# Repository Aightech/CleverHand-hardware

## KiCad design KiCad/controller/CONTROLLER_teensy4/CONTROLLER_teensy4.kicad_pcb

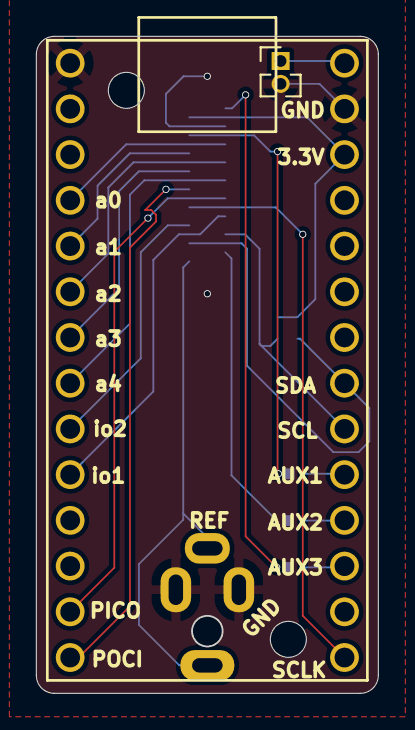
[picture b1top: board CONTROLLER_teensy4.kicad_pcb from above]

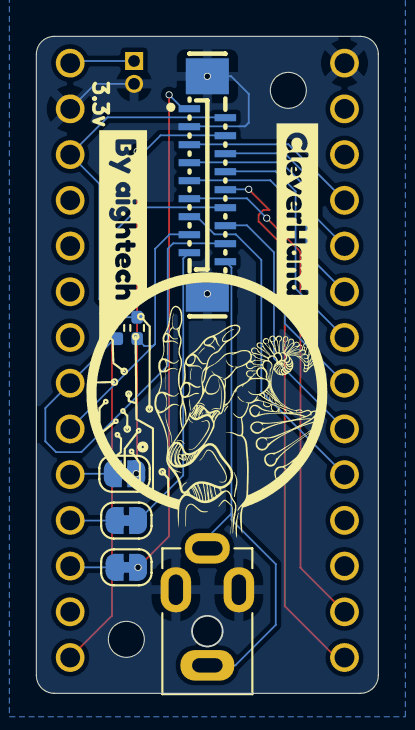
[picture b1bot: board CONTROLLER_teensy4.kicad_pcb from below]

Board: 4 copper layers, 19.0 x 36.5 mm, 11 parts (9 on the bottom side), 22 nets.

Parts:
FPC1: FPC-05F-18PH20; FPC-SMD_18P-P0.50_X05C2018TZ
J2: Conn_01x02_Pin; PinHeader_1x02_P1.27mm_Vertical
J5: jack2.5_PJ-210B; Jack_Socket_PJ-210B
JP1, JP2, JP3: SolderJumper_2_Bridged; SolderJumper-2_P1.3mm_Bridged_RoundedPad1.0x1.5mm
R1, R2: 2k; R_0402_1005Metric_Pad0.72x0.64mm_HandSolder
U1: Teensy4.0; Teensy40_simple
kibuzzard-6611AB09: G***; kibuzzard-6611AB09
kibuzzard-6611ABB8: G***; kibuzzard-6611ABB8

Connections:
+3.3V: FPC1.2, R1.1, R2.1, U1.31 (3V3)
/AUX1: FPC1.1, JP1.1 (A)
/AUX2: FPC1.17, JP2.1 (A)
/AUX3: FPC1.4, JP3.1 (A)
/I2C_SDA: FPC1.15, R2.2, U1.25 (18_A4_SDA0)
/IO1_out: FPC1.13, U1.10 (8_TX2_IN1)
/IO2: FPC1.14, U1.9 (7_RX2_OUT1A)
/PICO: FPC1.11, U1.13 (11_MOSI_CTX1)
/POCI: FPC1.10, U1.14 (12_MISO_MQSL)
/SCLK: FPC1.12, U1.20 (13_SCK_CRX1_LED)
/addr_bus_0: FPC1.5, U1.4 (2_OUT2)
/addr_bus_1: FPC1.6, U1.5 (3_LRCLK2)
/addr_bus_2: FPC1.7, U1.6 (4_BCLK2)
/addr_bus_3: FPC1.8, U1.7 (5_IN2)
/addr_bus_4: FPC1.9, U1.8 (6_OUT1D)
/extRef: FPC1.18, J5.2 (R), J5.6 (S)
/i2C_SCL: FPC1.16, R1.2, U1.26 (19_A5_SCL0)
GND: FPC1.3, FPC1.19, FPC1.20, J2.2, J5.1 (T), J5.3 (T), U1.1 (GND), U1.32 (GND)
unnamed: JP1.2 (B), U1.22 (15_A1_RX3_SPDIF_IN)
unnamed: JP2.2 (B), U1.23 (16_A2_RX4_SCL1)
unnamed: JP3.2 (B), U1.24 (17_A3_TX4_SDA1)
VSYS: J2.1, U1.33 (VIN)

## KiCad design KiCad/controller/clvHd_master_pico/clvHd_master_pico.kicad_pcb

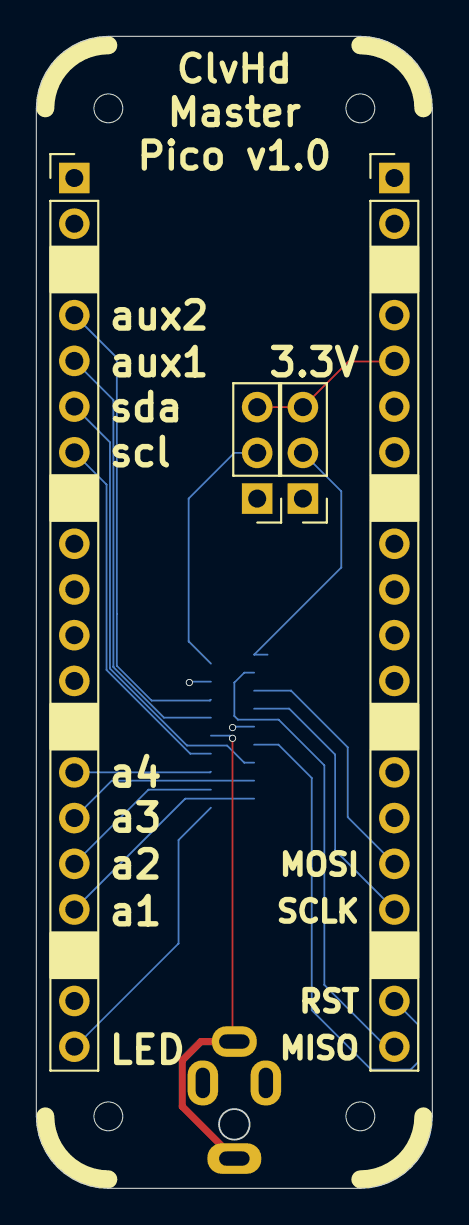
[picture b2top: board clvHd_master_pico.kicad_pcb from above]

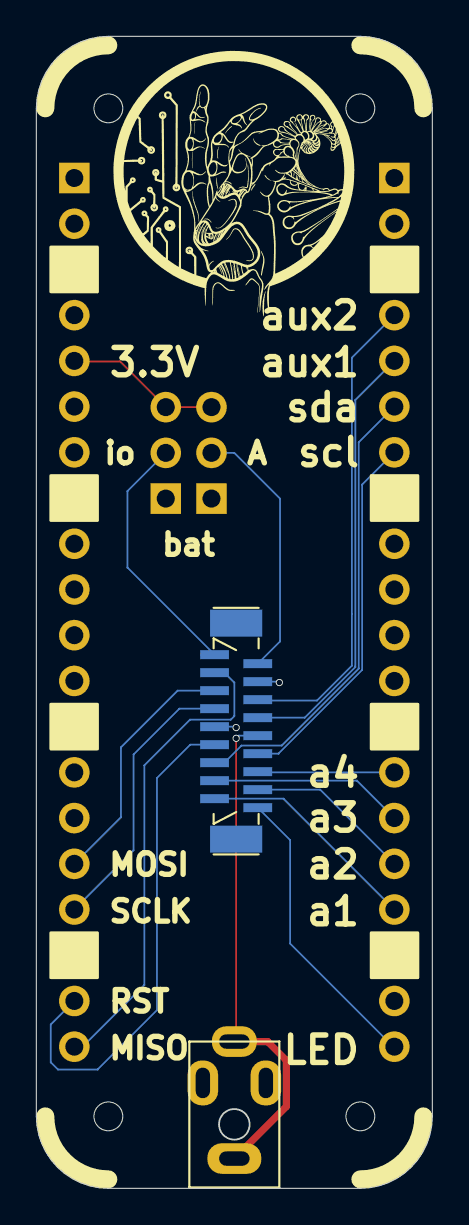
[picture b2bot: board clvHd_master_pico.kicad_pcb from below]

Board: 4 copper layers, 22.0 x 64.0 mm, 6 parts (2 on the bottom side), 18 nets.

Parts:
J1: XF2J-1824-12A
J3: jack2.5_PJ-210B; Jack_Socket_PJ-210B
J4, J5: Conn_01x20_Male; PinHeader_1x20_P2.54mm_Vertical
J6, J7: Conn_01x03_Male; PinHeader_1x03_P2.54mm_Vertical

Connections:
3V3_PICO: J5.5, J6.3, J7.3
+3.3V: J1.1, J7.2
+5VA: J1.2, J6.2
ADD_OUT1: J1.17, J4.17
ADD_OUT2: J1.16, J4.16
ADD_OUT3: J1.15, J4.15
ADD_OUT4: J1.14, J4.14
AUX1: J1.8, J4.5
AUX2: J1.6, J4.4
GND: J1.4, J1.9, J3.1 (T), J3.3 (T), J4.3, J4.8, J4.13, J4.18, J5.3, J5.8, J5.13, J5.18
I2C_SCL: J1.12, J4.7
I2C_SDA: J1.13, J4.6
IN_ref: J1.10, J3.2 (R), J3.6 (S)
LED_OUT: J1.18, J4.20
MISO_DOUT: J1.3, J5.20
MOSI_DIN: J1.5, J5.16
RESETB: J1.11, J5.19
SCLK: J1.7, J5.17

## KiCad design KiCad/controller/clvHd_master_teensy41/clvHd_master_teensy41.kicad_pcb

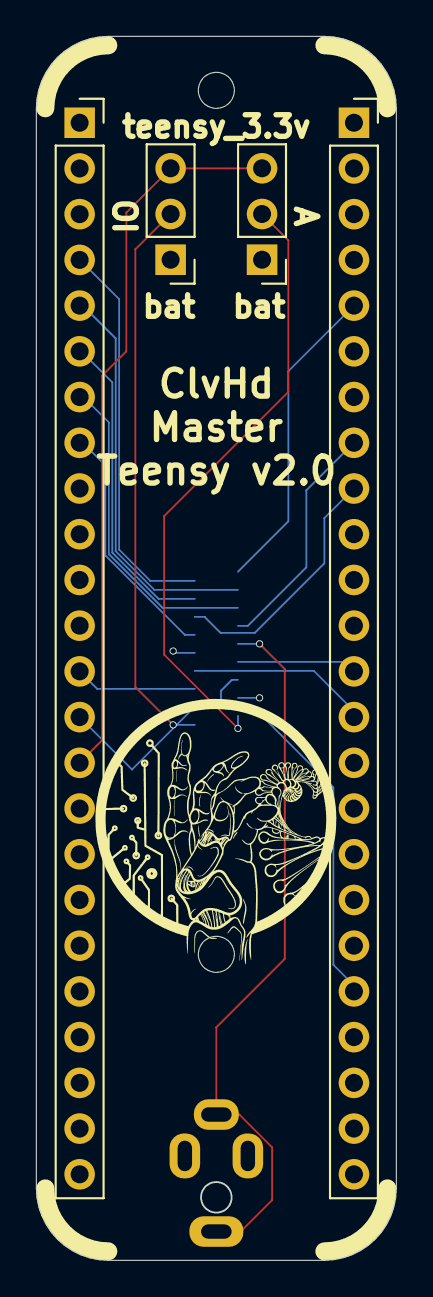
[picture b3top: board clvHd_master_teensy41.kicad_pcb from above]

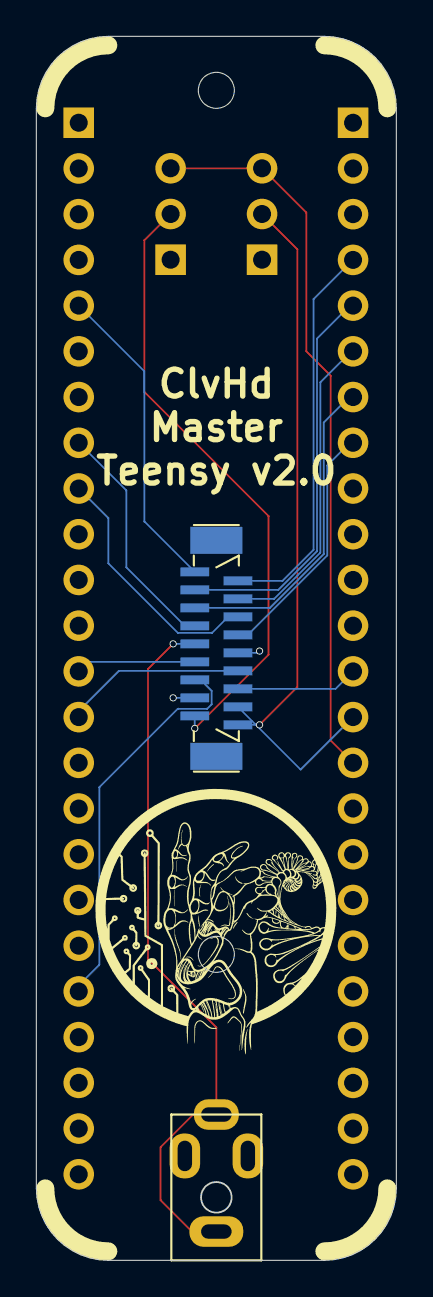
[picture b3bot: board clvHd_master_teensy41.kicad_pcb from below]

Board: 4 copper layers, 20.0 x 68.0 mm, 6 parts (2 on the bottom side), 18 nets.

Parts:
J1: XF2J-1824-12A
J2, J6: Conn_01x03_Male; PinHeader_1x03_P2.54mm_Vertical
J3: teensy_right; PinSocket_1x24_P2.54mm_Vertical
J4: teensy_left; PinSocket_1x24_P2.54mm_Vertical
J5: jack2.5_PJ-210B; Jack_Socket_PJ-210B

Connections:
3V3_TEENSY: J2.3, J4.15, J6.3
+3.3V: J1.1, J6.2
+5VA: J1.2, J2.2
ADD_OUT1: J1.17, J4.4
ADD_OUT2: J1.16, J4.5
ADD_OUT3: J1.15, J4.6
ADD_OUT4: J1.14, J4.7
AUX1: J1.8, J3.13
AUX2: J1.6, J3.20
GND: J1.4, J1.9, J3.2, J3.15, J4.1, J5.1 (T), J5.3 (T)
I2C_SCL: J1.12, J3.8
I2C_SDA: J1.13, J3.9
IN_ref: J1.10, J5.2 (R), J5.6 (S)
LED_OUT: J1.18, J3.5
MISO_DOUT: J1.3, J4.14
MOSI_DIN: J1.5, J4.13
RESETB: J1.11, J4.8
SCLK: J1.7, J3.14

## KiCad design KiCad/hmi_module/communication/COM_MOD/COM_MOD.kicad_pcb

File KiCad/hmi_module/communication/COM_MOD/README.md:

# Communication Module
This module is responsible for handling the communication between the different modules of the controller node.

The communication bus is composed of :
- Power supply (3.3V) and ground
- SPI bus (POCI, PICO, SCK)
- I2C bus (SDA, SCL)
- Address bus (A0, A1, A2, A3, A4)
- External reference voltage (AREF)

When the module is connected to the bus, it is assigned an address by the controller node. This address is used to identify the module on the bus.
The communication module will activate the chip select line of the associated sensor module when the address bus matches its address.
Additionally, each module has a unique identifier that is used to identify the module on the I2C bus.

## Electrical Schematic

## PCB Layout

## 3D Model

```stl
// COM_MOD_pcb.stl

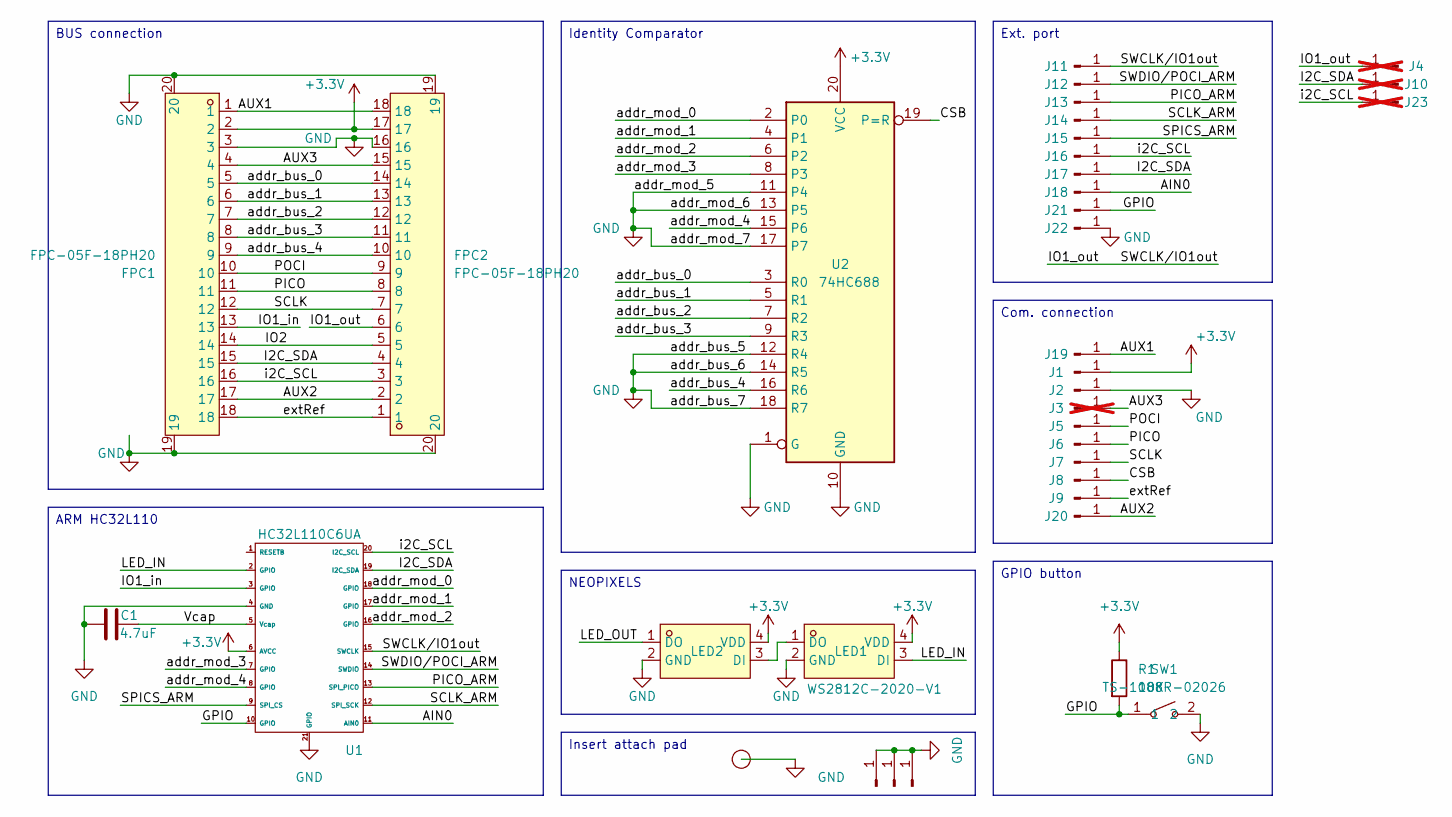
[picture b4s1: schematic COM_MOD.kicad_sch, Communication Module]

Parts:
C1: 4.7uF; C_0402_1005Metric; LCSC C23733
FPC1, FPC2: FPC-05F-18PH20; FPC-SMD_18P-P0.50_FPC-05F-18PH20; LCSC Part C2856802
I1: smd_insert; insert_1.2mm
J1, J2, J5, J6, J7, J8, J9, J11, J12, J13, J14, J15, J16, J17, J18, J19, J20, J21, J22: Conn_01x01_Pin; PinHeader_1x01_P1.27mm_Vertical
J3, J4, J10, J23: Conn_01x01_Pin; PinHeader_1x01_P1.27mm_Vertical; not fitted
J24, J25, J26: Conn_01x01_Pin; PinSocket_1x01_P2.54mm_Vertical
LED1: WS2812C-2020-V1; LED-SMD_4P-L2.0-W2.0-TL_WS2812B-2020; LCSC Part C2976072
LED2: WS2812C; LED-SMD_4P-L2.0-W2.0-TL_WS2812B-2020; LCSC Part C2976072
R1: 10K; R_0402_1005Metric; LCSC C25744
SW1: TS-1088R-02026; SW-SMD_L3.9-W3.0-P4.45; LCSC Part C455280
U1: HC32L110C6UA; QFN-20-1EP_3x3mm_P0.4mm_EP1.4x1.4mm; LCSC C493490
U2: 74HC688; TSSOP-20_W4.4mm; LCSC C132045

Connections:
+3.3V: FPC1.2, FPC2.17, J1.1, LED1.4 (VDD), LED2.4 (VDD), R1.1, U1.6 (AVCC), U2.20 (VCC)
/AIN0: J18.1, U1.11 (AIN0)
/AUX1: FPC1.1, FPC2.18, J19.1
/AUX2: FPC1.17, FPC2.2, J20.1
/AUX3: FPC1.4, FPC2.15, J3.1
/CSB: J8.1, U2.19 (P=R)
/GPIO: J21.1, R1.2, SW1.1, U1.10 (GPIO)
/I2C_SDA: FPC1.15, FPC2.4, J10.1, J17.1, U1.19 (I2C_SDA)
/IO1_in: FPC1.13, U1.3 (GPIO)
/IO1_out: FPC2.6, J4.1, J11.1, U1.15 (SWCLK)
/IO2: FPC1.14, FPC2.5
/LED_IN: LED1.3 (DI), U1.2 (GPIO)
/LED_OUT: LED2.1 (DO)
/PICO: FPC1.11, FPC2.8, J6.1
/PICO_ARM: J13.1, U1.13 (SPI_PICO)
/POCI: FPC1.10, FPC2.9, J5.1
/SCLK: FPC1.12, FPC2.7, J7.1
/SCLK_ARM: J14.1, U1.12 (SPI_SCK)
/SPICS_ARM: J15.1, U1.9 (SPI_CS)
/SWDIO/POCI_ARM: J12.1, U1.14 (SWDIO)
/Vcap: C1.2, U1.5 (Vcap)
/addr_bus_0: FPC1.5, FPC2.14, U2.3 (R0)
/addr_bus_1: FPC1.6, FPC2.13, U2.5 (R1)
/addr_bus_2: FPC1.7, FPC2.12, U2.7 (R2)
/addr_bus_3: FPC1.8, FPC2.11, U2.9 (R3)
/addr_bus_4: FPC1.9, FPC2.10, U2.16 (R6)
/addr_mod_0: U1.18 (GPIO), U2.2 (P0)
/addr_mod_1: U1.17 (GPIO), U2.4 (P1)
/addr_mod_2: U1.16 (GPIO), U2.6 (P2)
/addr_mod_3: U1.7 (GPIO), U2.8 (P3)
/addr_mod_4: U1.8 (GPIO), U2.15 (P6)
/extRef: FPC1.18, FPC2.1, J9.1
/i2C_SCL: FPC1.16, FPC2.3, J16.1, J23.1, U1.20 (I2C_SCL)
GND: C1.1, FPC1.3, FPC1.19, FPC1.20, FPC2.16, FPC2.19, FPC2.20, I1.1 (conn), J2.1, J22.1, J24.1, J25.1, J26.1, LED1.2 (GND), LED2.2 (GND), SW1.2, U1.4 (GND), U1.21 (GPIO), U2.1 (G), U2.10 (GND), U2.11 (P4), U2.12 (R4), U2.13 (P5), U2.14 (R5), U2.17 (P7), U2.18 (R7)
unnamed: LED1.1 (DO), LED2.3 (DI)

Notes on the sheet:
ARM HC32L110
Insert attach pad
NEOPIXELS
Identity Comparator
Com. connection
GPIO button
BUS connection
Ext. port

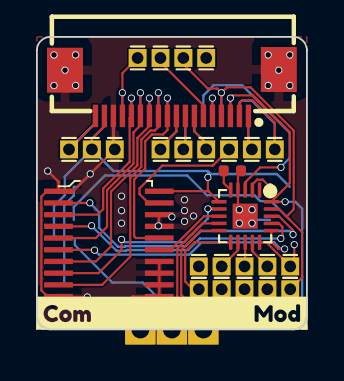
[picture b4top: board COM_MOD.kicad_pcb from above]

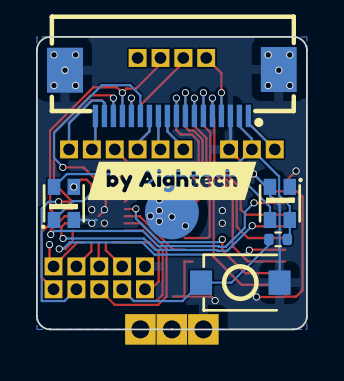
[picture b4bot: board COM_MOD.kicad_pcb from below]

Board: 4 copper layers, 15.0 x 16.3 mm, 38 parts (7 on the bottom side), 34 nets.

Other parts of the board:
kibuzzard-658C3FF8: G***; kibuzzard-658C3FF8
kibuzzard-658C2757: G***; kibuzzard-658C2757

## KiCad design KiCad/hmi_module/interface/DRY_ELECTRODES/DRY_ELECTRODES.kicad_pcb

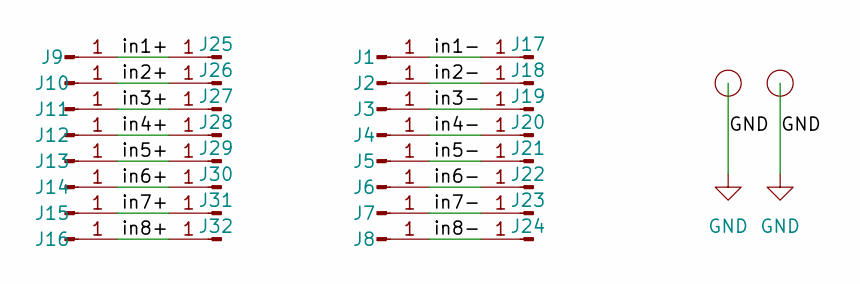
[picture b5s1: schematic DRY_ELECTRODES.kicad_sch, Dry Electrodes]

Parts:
I3, I4: smd_insert; insert_1.2mm
J1, J2, J3, J4, J5, J6, J7, J8, J9, J10, J11, J12, J13, J14, J15, J16: Conn_01x01_Pin; SolderWirePad_1x01_SMD_1x2mm
J17, J18, J19, J20, J21, J22, J23, J24, J25, J26, J27, J28, J29, J30, J31, J32: Conn_01x01_Pin; Pin_D1.2mm_pogo

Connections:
/in1+: J9.1, J25.1
/in1-: J1.1, J17.1
/in2+: J10.1, J26.1
/in2-: J2.1, J18.1
/in3+: J11.1, J27.1
/in3-: J3.1, J19.1
/in4+: J12.1, J28.1
/in4-: J4.1, J20.1
/in5+: J13.1, J29.1
/in5-: J5.1, J21.1
/in6+: J14.1, J30.1
/in6-: J6.1, J22.1
/in7+: J15.1, J31.1
/in7-: J7.1, J23.1
/in8+: J16.1, J32.1
/in8-: J8.1, J24.1
GND: I3.1 (conn), I4.1 (conn)

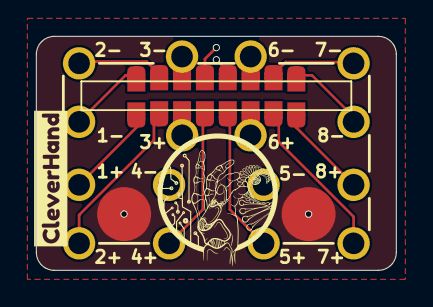
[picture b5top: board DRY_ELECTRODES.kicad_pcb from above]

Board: 4 copper layers, 20.0 x 13.0 mm, 35 parts (0 on the bottom side), 17 nets.

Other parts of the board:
kibuzzard-660706DE: G***; kibuzzard-660706DE

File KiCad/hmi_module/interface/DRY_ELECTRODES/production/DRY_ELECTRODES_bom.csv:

"Reference","Value","Footprint","DNP","LCSC"
"I3","smd_insert","00_custom-footprints:insert_1.2mm","",""
"I4","smd_insert","00_custom-footprints:insert_1.2mm","",""
"J1","Conn_01x01_Pin","00_custom-footprints:SolderWirePad_1x01_SMD_1x2mm","",""
"J2","Conn_01x01_Pin","00_custom-footprints:SolderWirePad_1x01_SMD_1x2mm","",""
"J3","Conn_01x01_Pin","00_custom-footprints:SolderWirePad_1x01_SMD_1x2mm","",""
"J4","Conn_01x01_Pin","00_custom-footprints:SolderWirePad_1x01_SMD_1x2mm","",""
"J5","Conn_01x01_Pin","00_custom-footprints:SolderWirePad_1x01_SMD_1x2mm","",""
"J6","Conn_01x01_Pin","00_custom-footprints:SolderWirePad_1x01_SMD_1x2mm","",""
"J7","Conn_01x01_Pin","00_custom-footprints:SolderWirePad_1x01_SMD_1x2mm","",""
"J8","Conn_01x01_Pin","00_custom-footprints:SolderWirePad_1x01_SMD_1x2mm","",""
"J9","Conn_01x01_Pin","00_custom-footprints:SolderWirePad_1x01_SMD_1x2mm","",""
"J10","Conn_01x01_Pin","00_custom-footprints:SolderWirePad_1x01_SMD_1x2mm","",""
"J11","Conn_01x01_Pin","00_custom-footprints:SolderWirePad_1x01_SMD_1x2mm","",""
"J12","Conn_01x01_Pin","00_custom-footprints:SolderWirePad_1x01_SMD_1x2mm","",""
"J13","Conn_01x01_Pin","00_custom-footprints:SolderWirePad_1x01_SMD_1x2mm","",""
"J14","Conn_01x01_Pin","00_custom-footprints:SolderWirePad_1x01_SMD_1x2mm","",""
"J15","Conn_01x01_Pin","00_custom-footprints:SolderWirePad_1x01_SMD_1x2mm","",""
"J16","Conn_01x01_Pin","00_custom-footprints:SolderWirePad_1x01_SMD_1x2mm","",""
"J17","Conn_01x01_Pin","00_custom-footprints:Pin_D1.2mm_pogo","",""
"J18","Conn_01x01_Pin","00_custom-footprints:Pin_D1.2mm_pogo","",""
"J19","Conn_01x01_Pin","00_custom-footprints:Pin_D1.2mm_pogo","",""
"J20","Conn_01x01_Pin","00_custom-footprints:Pin_D1.2mm_pogo","",""
"J21","Conn_01x01_Pin","00_custom-footprints:Pin_D1.2mm_pogo","",""
"J22","Conn_01x01_Pin","00_custom-footprints:Pin_D1.2mm_pogo","",""
"J23","Conn_01x01_Pin","00_custom-footprints:Pin_D1.2mm_pogo","",""
"J24","Conn_01x01_Pin","00_custom-footprints:Pin_D1.2mm_pogo","",""
"J25","Conn_01x01_Pin","00_custom-footprints:Pin_D1.2mm_pogo","",""
"J26","Conn_01x01_Pin","00_custom-footprints:Pin_D1.2mm_pogo","",""
"J27","Conn_01x01_Pin","00_custom-footprints:Pin_D1.2mm_pogo","",""
"J28","Conn_01x01_Pin","00_custom-footprints:Pin_D1.2mm_pogo","",""
"J29","Conn_01x01_Pin","00_custom-footprints:Pin_D1.2mm_pogo","",""
"J30","Conn_01x01_Pin","00_custom-footprints:Pin_D1.2mm_pogo","",""
"J31","Conn_01x01_Pin","00_custom-footprints:Pin_D1.2mm_pogo","",""
"J32","Conn_01x01_Pin","00_custom-footprints:Pin_D1.2mm_pogo","",""

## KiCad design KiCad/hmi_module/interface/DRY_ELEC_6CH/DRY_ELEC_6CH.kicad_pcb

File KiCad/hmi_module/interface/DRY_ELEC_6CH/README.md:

# Dry Electrodes Module
This module is responsible for interfacing the sensors/actuators inputs/outputs with the user skin or with other modules.

## Electrical Schematic

## PCB Layout

## 3D Model

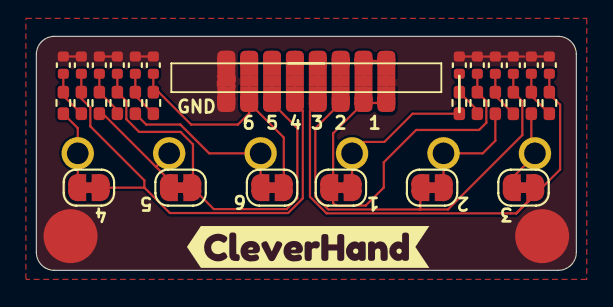
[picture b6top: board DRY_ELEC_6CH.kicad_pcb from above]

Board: 4 copper layers, 30.0 x 13.0 mm, 55 parts (0 on the bottom side), 19 nets.

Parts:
C1, C2, C3, C4, C5, C6, C7, C8, C9, C10, C11, C12: C; C_0402_1005Metric
I3, I4: smd_insert; insert_1.2mm
J1, J2, J3, J4, J5, J6, J7, J8, J9, J10, J11, J12, J13, J14, J15, J16: Conn_01x01_Pin; SolderWirePad_1x01_SMD_1x2mm
J17, J18, J19, J20, J21, J22: Conn_01x01_Pin; Pin_D1.2mm_pogo
JP1, JP2, JP3, JP4, JP5, JP6: SolderJumper_2_Bridged; SolderJumper-2_P1.3mm_Bridged_RoundedPad1.0x1.5mm
R1, R2, R3, R4, R5, R6, R7, R8, R9, R10, R11, R12: R; R_0402_1005Metric_Pad0.72x0.64mm_HandSolder
kibuzzard-66BA2E59: G***; kibuzzard-66BA2E59

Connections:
/IN1: C2.1, J7.1, J8.1, J15.1, J16.1, JP1.2 (B), R2.2
/IN2: C4.1, J6.1, J14.1, JP2.2 (B), R4.2
/IN3: C6.1, J5.1, J13.1, JP3.2 (B), R6.2
/IN4: C8.1, J4.1, J12.1, JP4.2 (B), R8.2
/IN5: C10.1, J3.1, J11.1, JP5.2 (B), R10.2
/IN6: C12.1, J2.1, J10.1, JP6.2 (B), R12.2
/filtering_1/ELECTRODE: J17.1, JP1.1 (A), R1.1
/filtering_2/ELECTRODE: J18.1, JP2.1 (A), R3.1
/filtering_3/ELECTRODE: J19.1, JP3.1 (A), R5.1
/filtering_4/ELECTRODE: J20.1, JP4.1 (A), R7.1
/filtering_5/ELECTRODE: J21.1, JP5.1 (A), R9.1
/filtering_6/ELECTRODE: J22.1, JP6.1 (A), R11.1
GND: C1.2, C2.2, C3.2, C4.2, C5.2, C6.2, C7.2, C8.2, C9.2, C10.2, C11.2, C12.2, I3.1 (conn), I4.1 (conn), J1.1, J9.1
unnamed: C1.1, R1.2, R2.1
unnamed: C3.1, R3.2, R4.1
unnamed: C5.1, R5.2, R6.1
unnamed: C7.1, R7.2, R8.1
unnamed: C9.1, R9.2, R10.1
unnamed: C11.1, R11.2, R12.1

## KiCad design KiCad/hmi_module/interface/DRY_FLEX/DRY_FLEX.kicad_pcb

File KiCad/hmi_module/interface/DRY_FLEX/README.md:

# Communication Module
This module extends the electrodes module. It a flexible PCB that connects the electrodes module and offers a flexible interface to the user.

## Electrical Schematic

## PCB Layout

## 3D Model

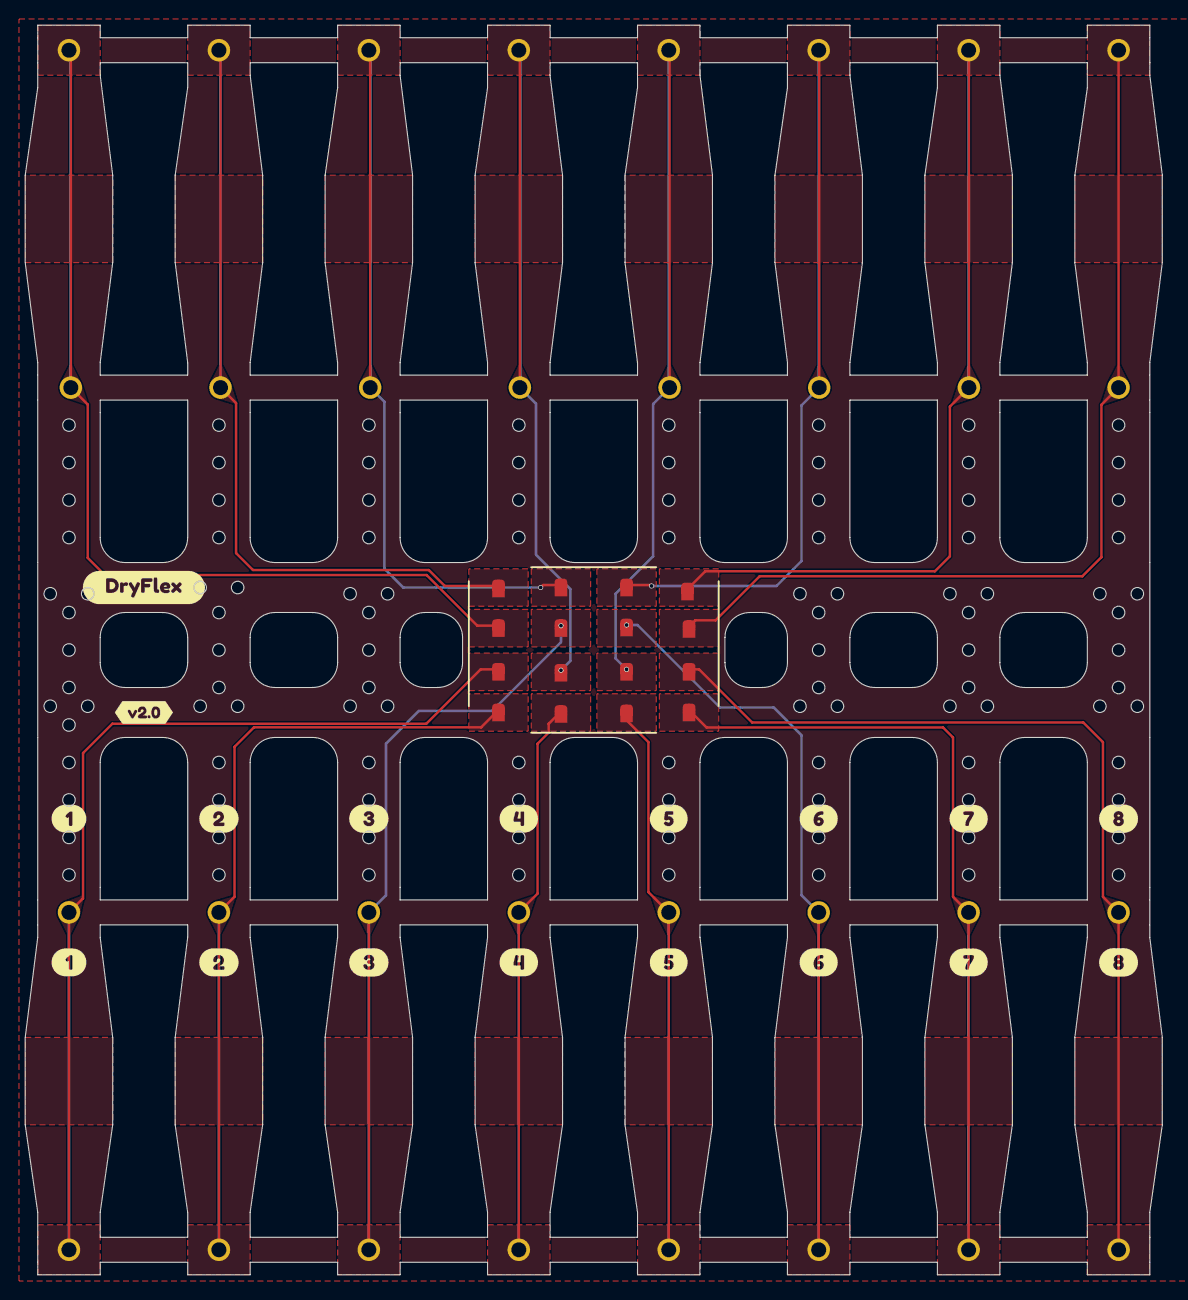
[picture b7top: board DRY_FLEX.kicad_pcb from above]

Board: 2 copper layers, 91.0 x 100.0 mm, 67 parts (1 on the bottom side), 16 nets.

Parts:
J1, J2, J3, J4, J5, J6, J7, J8, J9, J10, J11, J12, J13, J14, J15, J16, J17, J18, J19, J20, J21, J22, J23, J24, J25, J26, J27, J28, J29, J30, J31, J32: Conn_01x01_Pin; Pin_D1.2mm_pogo
TP1, TP2, TP3, TP4, TP5, TP6, TP7, TP8, TP9, TP10, TP11, TP12, TP13, TP14, TP15, TP16: TestPoint; SolderWirePad_1x01_SMD_1x2mm
kibuzzard-658EC94F, kibuzzard-658EC94F#2: G***; kibuzzard-658EC94F
kibuzzard-658EC95B, kibuzzard-658EC95B#2: G***; kibuzzard-658EC95B
kibuzzard-658EC936, kibuzzard-658EC936#2: G***; kibuzzard-658EC936
kibuzzard-658EC955, kibuzzard-658EC955#2: G***; kibuzzard-658EC955
kibuzzard-658EC960, kibuzzard-658EC960#2: G***; kibuzzard-658EC960
kibuzzard-66085B0B, kibuzzard-66085B0B#2: G***; kibuzzard-66085B0B
kibuzzard-66085B03, kibuzzard-66085B03#2: G***; kibuzzard-66085B03
kibuzzard-66085B10, kibuzzard-66085B10#2: G***; kibuzzard-66085B10
kibuzzard-66085C02: G***; kibuzzard-66085C02
kibuzzard-660866D6: G***; kibuzzard-660866D6
kibuzzard-6608669B: G***; kibuzzard-6608669B

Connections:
/in1+: J1.1, J17.1, TP9.1
/in1-: J9.1, J25.1, TP1.1
/in2+: J2.1, J18.1, TP10.1
/in2-: J10.1, J26.1, TP2.1
/in3+: J3.1, J19.1, TP11.1
/in3-: J11.1, J27.1, TP3.1
/in4+: J4.1, J20.1, TP12.1
/in4-: J12.1, J28.1, TP4.1
/in5+: J5.1, J21.1, TP13.1
/in5-: J13.1, J29.1, TP5.1
/in6+: J6.1, J22.1, TP14.1
/in6-: J14.1, J30.1, TP6.1
/in7+: J7.1, J23.1, TP15.1
/in7-: J15.1, J31.1, TP7.1
/in8+: J8.1, J24.1, TP16.1
/in8-: J16.1, J32.1, TP8.1

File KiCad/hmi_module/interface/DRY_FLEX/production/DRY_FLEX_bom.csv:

"Reference","Value","Footprint","DNP","LCSC"
"J1","Conn_01x01_Pin","00_custom-footprints:Pin_D1.2mm_pogo","",""
"J2","Conn_01x01_Pin","00_custom-footprints:Pin_D1.2mm_pogo","",""
"J3","Conn_01x01_Pin","00_custom-footprints:Pin_D1.2mm_pogo","",""
"J4","Conn_01x01_Pin","00_custom-footprints:Pin_D1.2mm_pogo","",""
"J5","Conn_01x01_Pin","00_custom-footprints:Pin_D1.2mm_pogo","",""
"J6","Conn_01x01_Pin","00_custom-footprints:Pin_D1.2mm_pogo","",""
"J7","Conn_01x01_Pin","00_custom-footprints:Pin_D1.2mm_pogo","",""
"J8","Conn_01x01_Pin","00_custom-footprints:Pin_D1.2mm_pogo","",""
"J9","Conn_01x01_Pin","00_custom-footprints:Pin_D1.2mm_pogo","",""
"J10","Conn_01x01_Pin","00_custom-footprints:Pin_D1.2mm_pogo","",""
"J11","Conn_01x01_Pin","00_custom-footprints:Pin_D1.2mm_pogo","",""
"J12","Conn_01x01_Pin","00_custom-footprints:Pin_D1.2mm_pogo","",""
"J13","Conn_01x01_Pin","00_custom-footprints:Pin_D1.2mm_pogo","",""
"J14","Conn_01x01_Pin","00_custom-footprints:Pin_D1.2mm_pogo","",""
"J15","Conn_01x01_Pin","00_custom-footprints:Pin_D1.2mm_pogo","",""
"J16","Conn_01x01_Pin","00_custom-footprints:Pin_D1.2mm_pogo","",""
"J17","Conn_01x01_Pin","00_custom-footprints:Pin_D1.2mm_pogo","",""
"J18","Conn_01x01_Pin","00_custom-footprints:Pin_D1.2mm_pogo","",""
"J19","Conn_01x01_Pin","00_custom-footprints:Pin_D1.2mm_pogo","",""
"J20","Conn_01x01_Pin","00_custom-footprints:Pin_D1.2mm_pogo","",""
"J21","Conn_01x01_Pin","00_custom-footprints:Pin_D1.2mm_pogo","",""
"J22","Conn_01x01_Pin","00_custom-footprints:Pin_D1.2mm_pogo","",""
"J23","Conn_01x01_Pin","00_custom-footprints:Pin_D1.2mm_pogo","",""
"J24","Conn_01x01_Pin","00_custom-footprints:Pin_D1.2mm_pogo","",""
"J25","Conn_01x01_Pin","00_custom-footprints:Pin_D1.2mm_pogo","",""
"J26","Conn_01x01_Pin","00_custom-footprints:Pin_D1.2mm_pogo","",""
"J27","Conn_01x01_Pin","00_custom-footprints:Pin_D1.2mm_pogo","",""
"J28","Conn_01x01_Pin","00_custom-footprints:Pin_D1.2mm_pogo","",""
"J29","Conn_01x01_Pin","00_custom-footprints:Pin_D1.2mm_pogo","",""
"J30","Conn_01x01_Pin","00_custom-footprints:Pin_D1.2mm_pogo","",""
"J31","Conn_01x01_Pin","00_custom-footprints:Pin_D1.2mm_pogo","",""
"J32","Conn_01x01_Pin","00_custom-footprints:Pin_D1.2mm_pogo","",""
"TP1","TestPoint","00_custom-footprints:SolderWirePad_1x01_SMD_1x2mm","",""
"TP2","TestPoint","00_custom-footprints:SolderWirePad_1x01_SMD_1x2mm","",""
"TP3","TestPoint","00_custom-footprints:SolderWirePad_1x01_SMD_1x2mm","",""
"TP4","TestPoint","00_custom-footprints:SolderWirePad_1x01_SMD_1x2mm","",""
"TP5","TestPoint","00_custom-footprints:SolderWirePad_1x01_SMD_1x2mm","",""
"TP6","TestPoint","00_custom-footprints:SolderWirePad_1x01_SMD_1x2mm","",""
"TP7","TestPoint","00_custom-footprints:SolderWirePad_1x01_SMD_1x2mm","",""
"TP8","TestPoint","00_custom-footprints:SolderWirePad_1x01_SMD_1x2mm","",""
"TP9","TestPoint","00_custom-footprints:SolderWirePad_1x01_SMD_1x2mm","",""
"TP10","TestPoint","00_custom-footprints:SolderWirePad_1x01_SMD_1x2mm","",""
"TP11","TestPoint","00_custom-footprints:SolderWirePad_1x01_SMD_1x2mm","",""
"TP12","TestPoint","00_custom-footprints:SolderWirePad_1x01_SMD_1x2mm","",""
"TP13","TestPoint","00_custom-footprints:SolderWirePad_1x01_SMD_1x2mm","",""
"TP14","TestPoint","00_custom-footprints:SolderWirePad_1x01_SMD_1x2mm","",""
"TP15","TestPoint","00_custom-footprints:SolderWirePad_1x01_SMD_1x2mm","",""
"TP16","TestPoint","00_custom-footprints:SolderWirePad_1x01_SMD_1x2mm","",""
